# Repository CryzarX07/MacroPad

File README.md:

My 4-Key Macropad ProjectHi! This is a simple 4-key macropad I designed. It uses a Seeed Studio XIAO RP2040 and has two RGB lights that change color when you press different buttons.🛠 What you need (BOM)I used these parts for my build:1x Seeed Studio XIAO RP20402x SK6812 RGB LEDs (These are the lights)4x Push Buttons (Mechanical switches)📐 How it is wiredI connected everything to the XIAO board using these pins:PartPin on XIAOButton 1 (SW5)GP26Button 2 (SW1)GP27Button 3 (SW2)GP28Button 4 (SW3)GP29RGB LightsGP0💻 The SoftwareI used KMK Firmware (which runs on CircuitPython). It is very easy because you don't need to "compile" anything—you just save a text file.How it works:Button 1: Types "A" and turns the lights Red.Button 2: Presses "Delete" and turns the lights Green.Button 3: Types "Hello world!" and turns the lights Blue.Button 4: Presses "Cmd + S" (Save) and turns the lights Purple.The Code (main.py)Pythonimport board
from kmk.kmk_keyboard import KMKKeyboard
from kmk.scanners.keypad import KeysScanner
from kmk.keys import KC
from kmk.modules.macros import Macros
from kmk.extensions.rgb import RGB, AnimationModes

keyboard = KMKKeyboard()
macros = Macros()
keyboard.modules.append(macros)

rgb = RGB(
    pixel_pin=board.GP0,
    num_pixels=2,
    val=150,
    hue_default=0,
    sat_default=255,
    rgb_order=(1, 0, 2),
    animation_mode=AnimationModes.STATIC,
)
keyboard.extensions.append(rgb)

def make_red(keyboard):
    rgb.set_hsv(0, 255, 150)

def make_green(keyboard):
    rgb.set_hsv(85, 255, 150)

def make_blue(keyboard):
    rgb.set_hsv(170, 255, 150)

def make_purple(keyboard):
    rgb.set_hsv(200, 255, 150)

PINS = [board.GP26, board.GP27, board.GP28, board.GP29]

keyboard.matrix = KeysScanner(
    pins=PINS,
    value_when_pressed=False,
)

keyboard.keymap = [
    [
        KC.MACRO(make_red, KC.A),
        KC.MACRO(make_green, KC.DELETE),
        KC.MACRO(make_blue, "Hello world!"),
        KC.MACRO(make_purple, KC.LCMD(KC.S)),
    ]
]

if __name__ == '__main__':
    keyboard.go()

BOM: 
"ID";"Bezeichner";"Footprint";"Stückzahl";"Bezeichnung";"Anbieter und Referenz";
1;"D1,D3";"LED_SK6812MINI_PLCC4_3.5x3.5mm_P1.75mm";2;"SK6812";;;
2;"SW2,SW1,SW5,SW3";"SW_Cherry_MX_1.00u_PCB";4;"SW_Push";;;
3;"U1";"XIAO-RP2040-DIP";1;"XIAO-RP2040-DIP";;;

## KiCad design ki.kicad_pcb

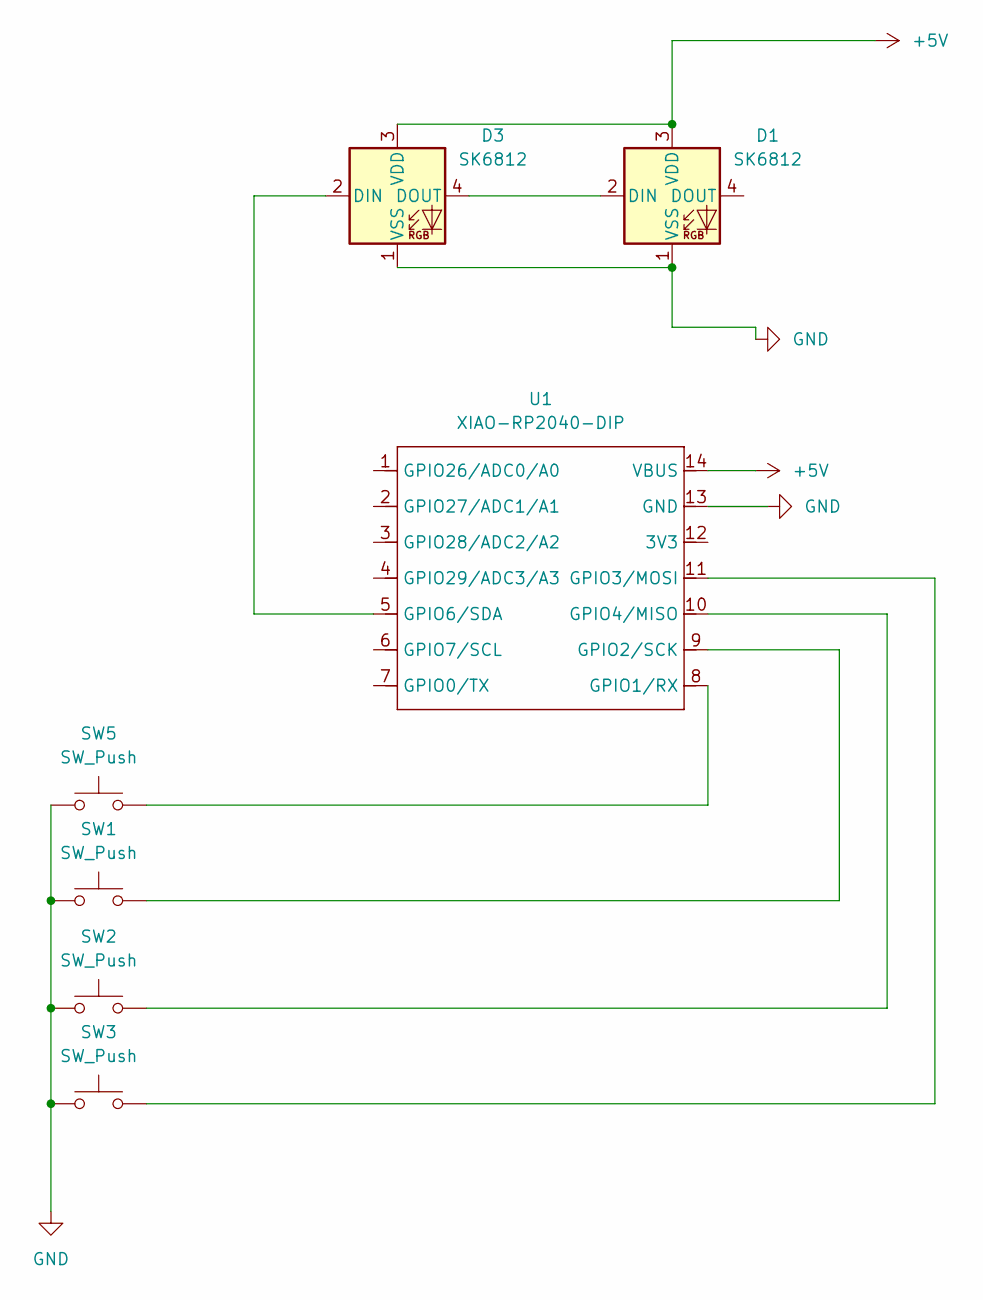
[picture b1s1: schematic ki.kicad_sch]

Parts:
D1, D3: SK6812; LED_SK6812MINI_PLCC4_3.5x3.5mm_P1.75mm
SW1, SW2, SW3, SW5: SW_Push; SW_Cherry_MX_1.00u_PCB
U1: XIAO-RP2040-DIP

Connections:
+5V: D1.3 (VDD), D3.3 (VDD), U1.14 (VBUS)
GND: D1.1 (VSS), D3.1 (VSS), SW1.1, SW2.1, SW3.1, SW5.1, U1.13 (GND)
unnamed: D1.2 (DIN), D3.4 (DOUT)
unnamed: D3.2 (DIN), U1.5 (GPIO6/SDA)
unnamed: SW5.2, U1.8 (GPIO1/RX)
unnamed: SW1.2, U1.9 (GPIO2/SCK)
unnamed: SW3.2, U1.11 (GPIO3/MOSI)
unnamed: SW2.2, U1.10 (GPIO4/MISO)

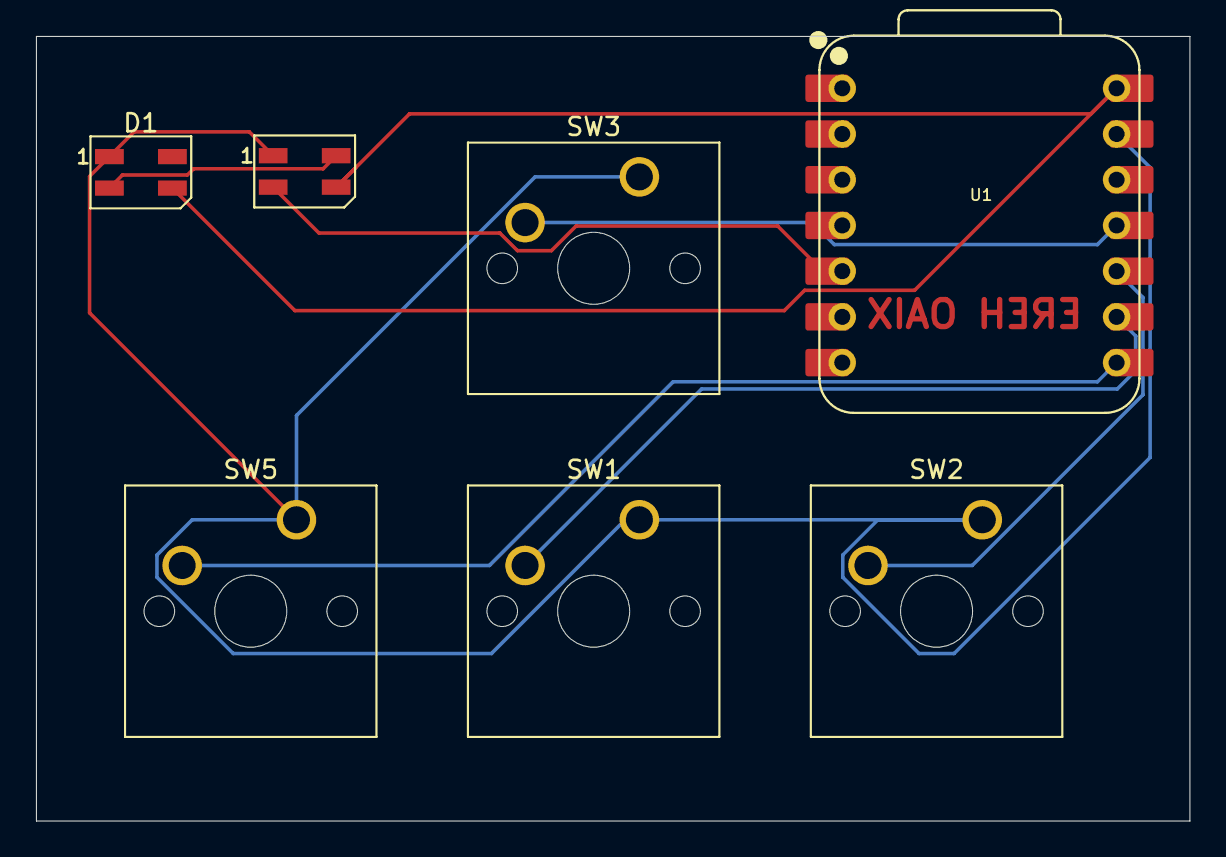
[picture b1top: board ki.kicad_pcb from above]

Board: 2 copper layers, 64.1 x 43.6 mm, 7 parts (0 on the bottom side), 8 nets.

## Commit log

2026-02-03 Create Firmware Macropad
2026-02-03 README.md
